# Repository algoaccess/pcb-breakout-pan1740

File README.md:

# pcb-breakout-pan1740
Pin breakout of the Panasonic PA1740 board to through-hole pin headers for prototyping.

##PCB Design software and addons used

1. Eagle 7.3.0: I use Standard but Light should still be able to open/modify the files.
2. PAN1740 library by [DIY modules](http://www.diymodules.org/eagle-show-library?type=usr&id=1012210994) (in repo as panasonic-pan1740.lbr)

##Images

This is the older revision 1 design. It has an error of some vias being below the antenna. Has been corrected in Revision 2.

##Schematic drawings
Images are exported from Eagle at 600dpi.

##Parts required

The PAN1740 module which can be bought from one of the online stores like [Mouser](http://www.mouser.sg/new/panasonic/panasonic-pan1740-ble-module/)

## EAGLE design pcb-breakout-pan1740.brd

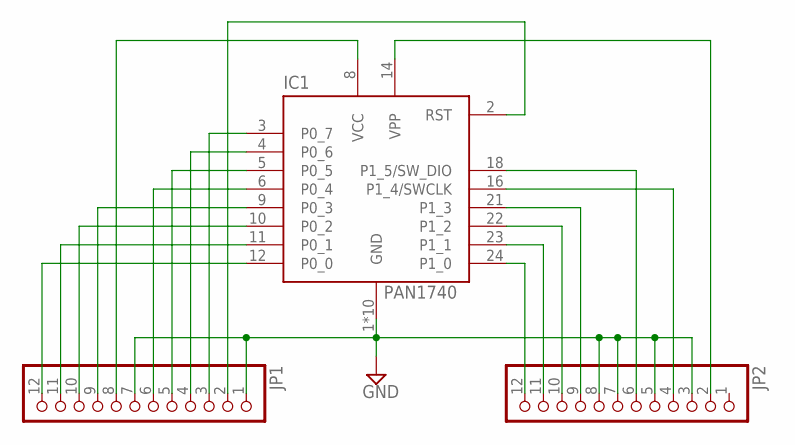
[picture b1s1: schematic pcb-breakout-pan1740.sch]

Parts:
IC1: PAN1740
JP1, JP2: PINHD-1X12; 1X12

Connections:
GND: IC1.1 (GND), IC1.7 (GND), IC1.15 (GND), IC1.17 (GND), IC1.19 (GND), IC1.20 (GND), IC1.A (GND), IC1.B (GND), IC1.C (GND), IC1.D (GND), JP1.1, JP1.7, JP2.3, JP2.5, JP2.7, JP2.8
unnamed: IC1.2 (RST), JP1.2
unnamed: IC1.3 (P0_7), JP1.3
unnamed: IC1.4 (P0_6), JP1.4
unnamed: IC1.5 (P0_5), JP1.5
unnamed: IC1.6 (P0_4), JP1.6
unnamed: IC1.8 (VCC), JP1.8
unnamed: IC1.9 (P0_3), JP1.9
unnamed: IC1.10 (P0_2), JP1.10
unnamed: IC1.11 (P0_1), JP1.11
unnamed: IC1.12 (P0_0), JP1.12
unnamed: IC1.14 (VPP), JP2.2
unnamed: IC1.16 (P1_4/SWCLK), JP2.4
unnamed: IC1.18 (P1_5/SW_DIO), JP2.6
unnamed: IC1.21 (P1_3), JP2.9
unnamed: IC1.22 (P1_2), JP2.10
unnamed: IC1.23 (P1_1), JP2.11
unnamed: IC1.24 (P1_0), JP2.12

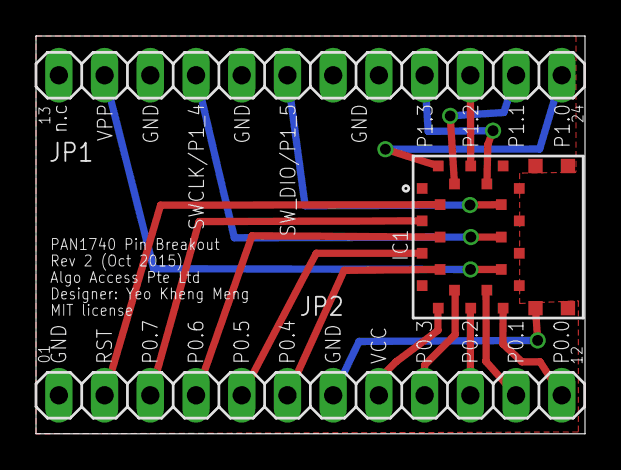
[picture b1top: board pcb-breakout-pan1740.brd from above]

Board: 2 copper layers, 30.5 x 22.1 mm, 3 parts (0 on the bottom side), 18 nets.

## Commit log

2015-10-10 polygon adjustment
2015-10-10 silkscreen
2015-10-10 more silkscreen text
2015-10-19 corrected error in silkscreen pin number
2015-10-19 up to rev 2
2015-10-19 reduce size of schematic
2015-10-19 images and gerbels
2015-10-19 rev2 gerbel
2015-10-20 position of pan1740
2015-10-20 nev rev 2 gerbel
2015-10-22 front image
2015-10-22 rev 2 board image

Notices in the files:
pcb-breakout-pan1740.brd:
MIT license
